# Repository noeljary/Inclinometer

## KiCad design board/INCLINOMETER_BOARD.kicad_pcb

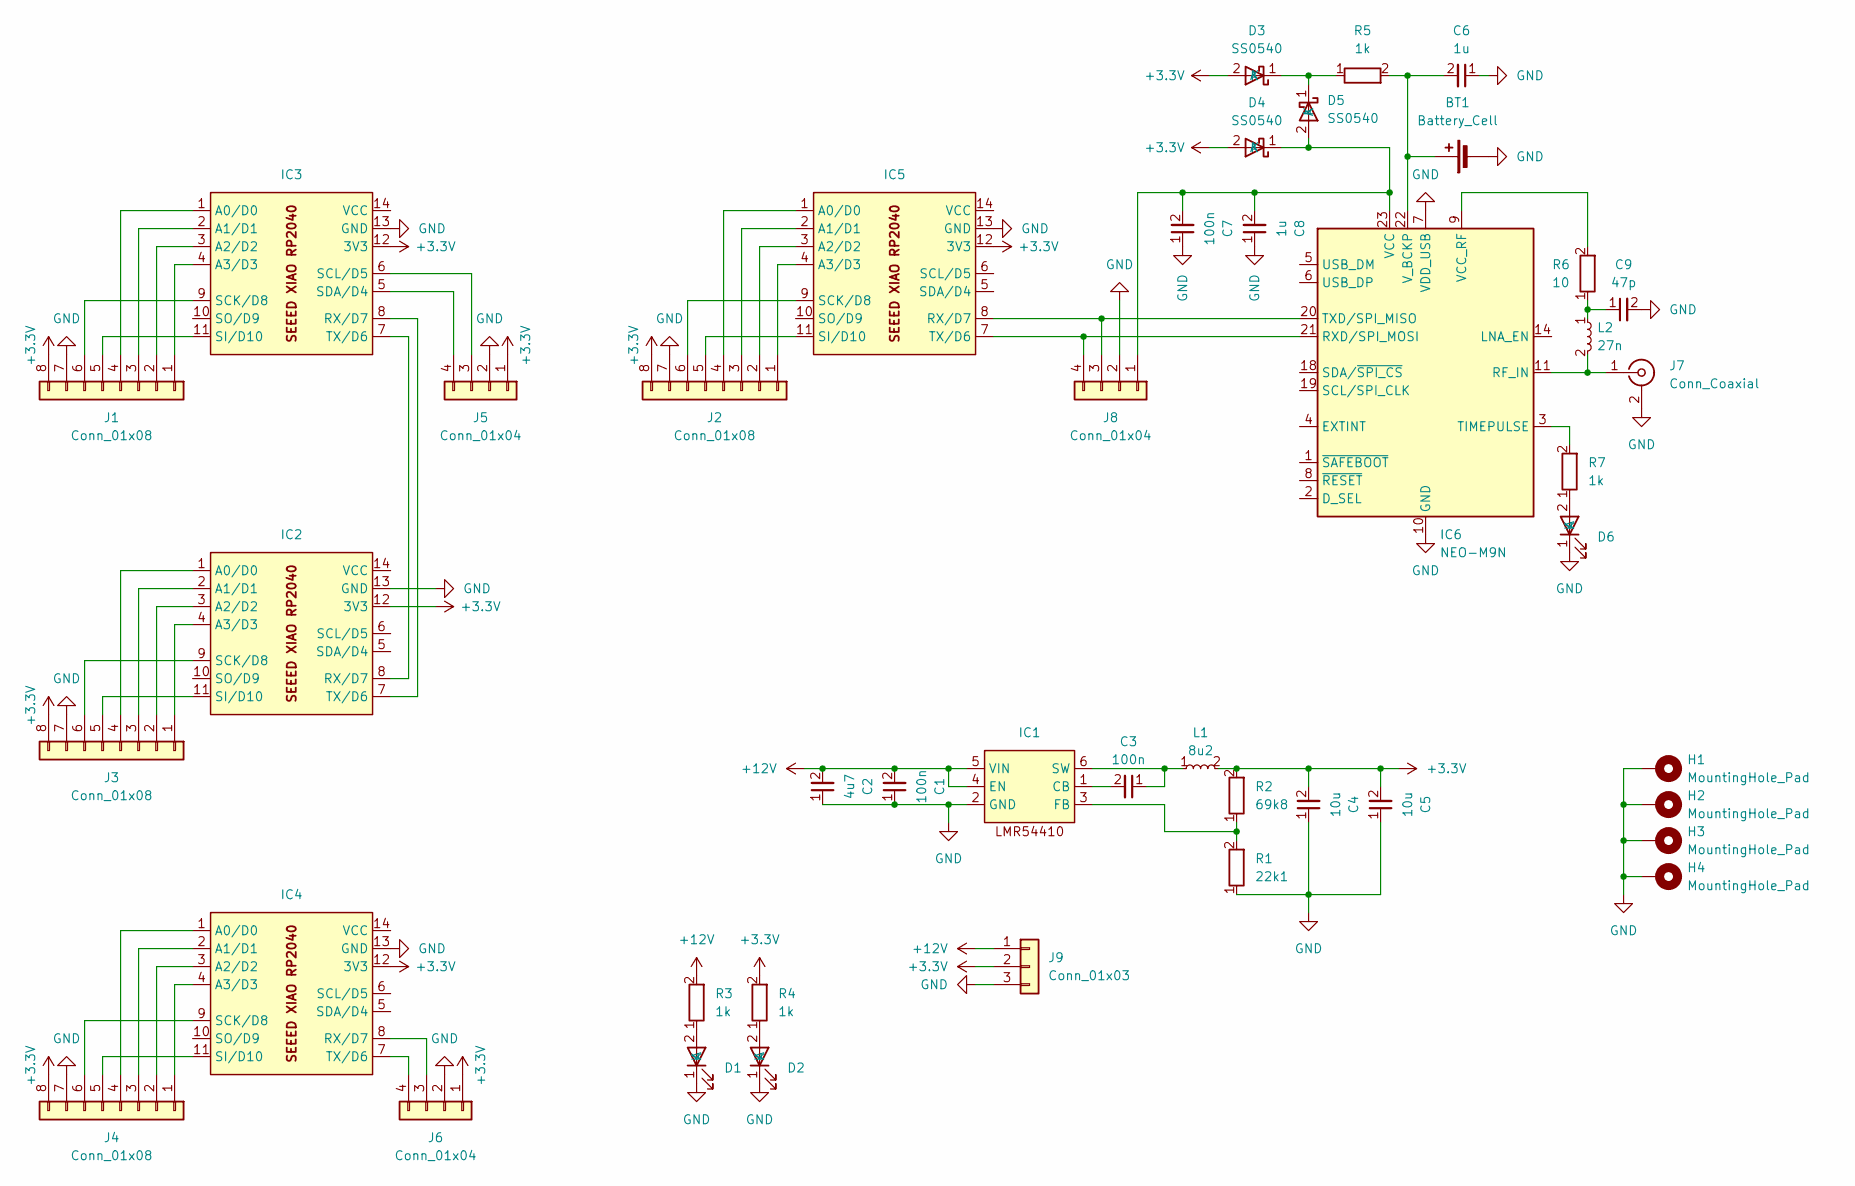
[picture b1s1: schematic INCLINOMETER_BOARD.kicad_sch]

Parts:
BT1: Battery_Cell; BAT-MS621
C1, C3, C7: 100n; C0805
C2: 4u7; C0805
C4, C5: 10u; C0805
C6, C8: 1u; C0805
C9: 47p; C0805
D1, D2, D6: 1206
D3, D4, D5: SS0540; SOD-123
H1, H2, H3, H4: MountingHole_Pad; MountingHole_3.2mm_M3_Pad_Via
IC1: SOT23-6
IC2, IC3, IC4, IC5: SEEED_XIAO
IC6: NEO-M9N; UBLOX-NEO-M9N
J1, J2, J3, J4: Conn_01x08; TE-292228-8
J5, J6, J8: Conn_01x04; TE-292228-4
J7: Conn_Coaxial; FAKRA_R197.160._28
J9: Conn_01x03; MICROFIT3.0-1x3-HORIZ
L1: 8u2; L6055
L2: 27n; L0805
R1: 22k1; R0805
R2: 69k8; R0805
R3, R4, R5, R7: 1k; R0805
R6: 10; R0805

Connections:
+3.3V: C4.2, C5.2, D3.2 (A), D4.2 (A), IC2.12 (3V3), IC3.12 (3V3), IC4.12 (3V3), IC5.12 (3V3), J1.8, J2.8, J3.8, J4.8, J5.1, J6.1, J9.2, L1.2, R2.2, R4.2
+12V: C1.2, C2.2, IC1.4 (EN), IC1.5 (VIN), J9.1, R3.2
GND: BT1.2 (-), C1.1, C2.1, C4.1, C5.1, C6.1, C7.1, C8.1, C9.2, D1.1 (K), D2.1 (K), D6.1 (K), H1.1, H2.1, H3.1, H4.1, IC1.2 (GND), IC2.13 (GND), IC3.13 (GND), IC4.13 (GND), IC5.13 (GND), IC6.7 (VDD_USB), IC6.10 (GND), IC6.12 (GND), IC6.13 (GND), IC6.24 (GND), J1.7, J2.7, J3.7, J4.7, J5.2, J6.2, J7.2 (Ext), J8.2, J9.3, R1.1
unnamed: BT1.1 (+), C6.2, IC6.22 (V_BCKP), R5.2
unnamed: C9.1, L2.1, R6.1
unnamed: D1.2 (A), R3.1
unnamed: D2.2 (A), R4.1
unnamed: D3.1 (K), D5.1 (K), R5.1
unnamed: C7.2, C8.2, D4.1 (K), D5.2 (A), IC6.23 (VCC), J8.1
unnamed: D6.2 (A), R7.1
unnamed: C3.2, IC1.1 (CB)
unnamed: IC1.3 (FB), R1.2, R2.1
unnamed: C3.1, IC1.6 (SW), L1.1
unnamed: IC2.1 (A0/D0), J3.4
unnamed: IC2.2 (A1/D1), J3.3
unnamed: IC2.3 (A2/D2), J3.2
unnamed: IC2.4 (A3/D3), J3.1
unnamed: IC2.8 (RX/D7), IC3.7 (TX/D6)
unnamed: IC2.9 (SCK/D8), J3.6
unnamed: IC2.11 (SI/D10), J3.5
unnamed: IC2.7 (TX/D6), IC3.8 (RX/D7)
unnamed: IC3.1 (A0/D0), J1.4
unnamed: IC3.2 (A1/D1), J1.3
unnamed: IC3.3 (A2/D2), J1.2
unnamed: IC3.4 (A3/D3), J1.1
unnamed: IC3.9 (SCK/D8), J1.6
unnamed: IC3.6 (SCL/D5), J5.3
unnamed: IC3.5 (SDA/D4), J5.4
unnamed: IC3.11 (SI/D10), J1.5
unnamed: IC4.1 (A0/D0), J4.4
unnamed: IC4.2 (A1/D1), J4.3
unnamed: IC4.3 (A2/D2), J4.2
unnamed: IC4.4 (A3/D3), J4.1
unnamed: IC4.8 (RX/D7), J6.3
unnamed: IC4.9 (SCK/D8), J4.6
unnamed: IC4.11 (SI/D10), J4.5
unnamed: IC4.7 (TX/D6), J6.4
unnamed: IC5.1 (A0/D0), J2.4
unnamed: IC5.2 (A1/D1), J2.3
unnamed: IC5.3 (A2/D2), J2.2
unnamed: IC5.4 (A3/D3), J2.1
unnamed: IC5.8 (RX/D7), IC6.20 (TXD/SPI_MISO), J8.3
unnamed: IC5.9 (SCK/D8), J2.6
unnamed: IC5.11 (SI/D10), J2.5
unnamed: IC5.7 (TX/D6), IC6.21 (RXD/SPI_MOSI), J8.4
unnamed: IC6.11 (RF_IN), J7.1 (In), L2.2
unnamed: IC6.3 (TIMEPULSE), R7.2
unnamed: IC6.9 (VCC_RF), R6.2

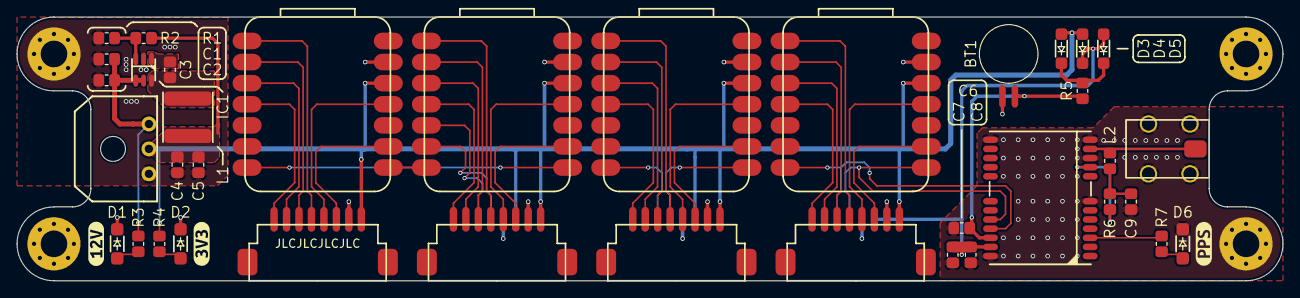
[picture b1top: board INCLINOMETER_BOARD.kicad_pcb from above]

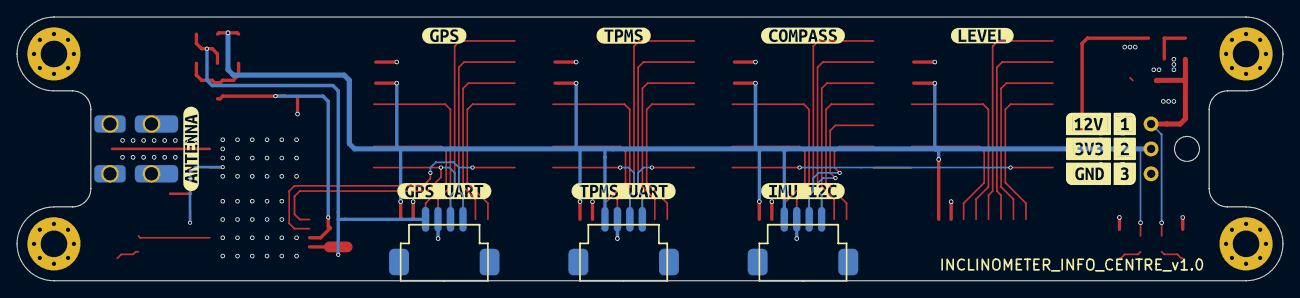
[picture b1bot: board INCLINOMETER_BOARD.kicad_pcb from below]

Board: 4 copper layers, 152.4 x 31.8 mm, 61 parts (17 on the bottom side), 48 nets.

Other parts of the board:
kibuzzard-64DFFC28: G***; kibuzzard-64DFFC28
kibuzzard-64EF6B93: G***; kibuzzard-64EF6B93
kibuzzard-64EF6BB1: G***; kibuzzard-64EF6BB1
kibuzzard-64EF6BC1: G***; kibuzzard-64EF6BC1
kibuzzard-64EF9CA5: G***; kibuzzard-64EF9CA5
kibuzzard-64EF9CAD: G***; kibuzzard-64EF9CAD
kibuzzard-64EF9D40: G***; kibuzzard-64EF9D40
kibuzzard-64EF9D48: G***; kibuzzard-64EF9D48
kibuzzard-64EF9D56: G***; kibuzzard-64EF9D56
kibuzzard-64EFA0F6: G***; kibuzzard-64EFA0F6
kibuzzard-64EFA8FB: G***; kibuzzard-64EFA8FB
kibuzzard-64F4D53D: G***; kibuzzard-64F4D53D
kibuzzard-64F4D513: G***; kibuzzard-64F4D513
kibuzzard-64F4D629: G***; kibuzzard-64F4D629
kibuzzard-650ECDA2: G***; kibuzzard-650ECDA2
kibuzzard-650ECDAE: G***; kibuzzard-650ECDAE
kibuzzard-65062FEF: G***; kibuzzard-65062FEF

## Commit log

2021-07-15 Initial commit of basic compass/pitch/roll to serial output
2022-12-02 Post POC commit with modularised components
2022-12-03 Add circuit schematics and board
2022-12-23 Sort bug where lat/lng show negative despite having relevant cardinal
2022-12-23 Update vertical element alignment
2022-12-23 Fix introduced tab whitespace
2023-11-25 Migrated board design into KiCAD7 from EAGLE. v1.0 of manufactured board including gerber files
2023-11-25 Rewritten TPMS Display in Micropythin for vastly superior performance
2023-11-25 Mock tool for TPMS system - sends data to TPMS Display as if it had received it wirelessly for testing purposes
2023-11-25 Attaching micropython binary compiled for RP2040, including C driver for GC9A01 and updated framebuffer with bitmap image and font support
2023-11-25 Adding initial revision of GPS module code in micropython. Needs refactoring to same framework level as TPMS Display
2023-11-25 First revision of TPMS Wirelss Receiver code. Refactored version of JSMSolns 'Arduino TPMS Tyre Pressure Display' - removed all display logic, and unnecessary parts, initially only supports Toyota PM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
2023-11-25 Refactored to TPMS Display Standard. Series of GPS Parsing Library bug fixes.
2023-11-26 Added units management to GPS screens with file saving for persistance
2023-11-26 Fix what seems to be a find/replace issue in TPMS code but no idea how it got there
2023-11-27 Added blueprint for Timezone management
